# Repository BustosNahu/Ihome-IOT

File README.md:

# IHOME (spanish)

Este proyecto consta de una app con la cual deberias poder manejar toda tu casa,
hasta el momento serian cerraduras, camaras, y posibles cortinas .
El mismo posee desarrollo de hardware y modelado 3d de las cerraduras IOT.

## Tecnologias usadas

-   APLICACION MOVIL ANDROID 
En cuanto al desarrollo de la App mobile, la misma esta siendo desarrollada en idioma nativo Java, mediante la IDE de Android Studio. Estando solo disponible para dispotivios Android.

- APLICACION WEB

-   MICROCONTROLADOR
En cuanto al microcontrolador usado para la cerradura IOT de Ihome, fue utilizado un modulo ESP32s, el cual posee una antena para poder conectarse a la red wifi. 
El mismo fue programado en C++ con Arduino IDE. 

-   ESTUDIO Y DISEÑO UX/UI
La aplicacion de Ihome fue diseñada por un equipo certificado en UX/UI, creada y estudiada para un arquetipo de persona en especial, 
y que el publico de Ihome sienta una mayor comodidad y experiencia de usuario al utilizar la aplicacion. 

-   BASE DE DATOS
Ihome utiliza Firebase como base de datos para poder guardar toda su informacion. Desde fotos, datos de usuario, dispositivos vinculados entorno a la app mobile, y 
en torno a los micro controladores Firebase es utilizada para obtener los estados de los datos cargados por el usuario.

-   MODELADO 3D
El modelado 3d de Ihome fue llevado a cabo mediante la plataforma de modelado Fusion 360 de Auto Desk. 
Hasta el momento fue unicamente diseñado el modelo de la cerradura IOT. 

-   DISEÑO DE PCB ("Printed Circuit Board")
El diseño de PCB de Ihome fue llevado a cabo en la plataforma de Kicad, donde tuve que descargar los footprints de los componentes, modelos 3d, etc. 
Ya que la misma tiene un render que te permite ver los diseños en 3d. Ese mismo PCB terminado lo exportamos de Kicad y lo importamos en Fusion 360, 
para realizar un modelado 3d mas eficaz. 

## 🔗 Desarrolladores Links
- Desarrollador general del proyecto: 

Nahuel Alexander Bustos 

- Estudio y diseño del UX/UI:

Micaela Natasha Bustos

- Desarrollador de la aplicacion web del microcontrolador:

Joaquin Cervio

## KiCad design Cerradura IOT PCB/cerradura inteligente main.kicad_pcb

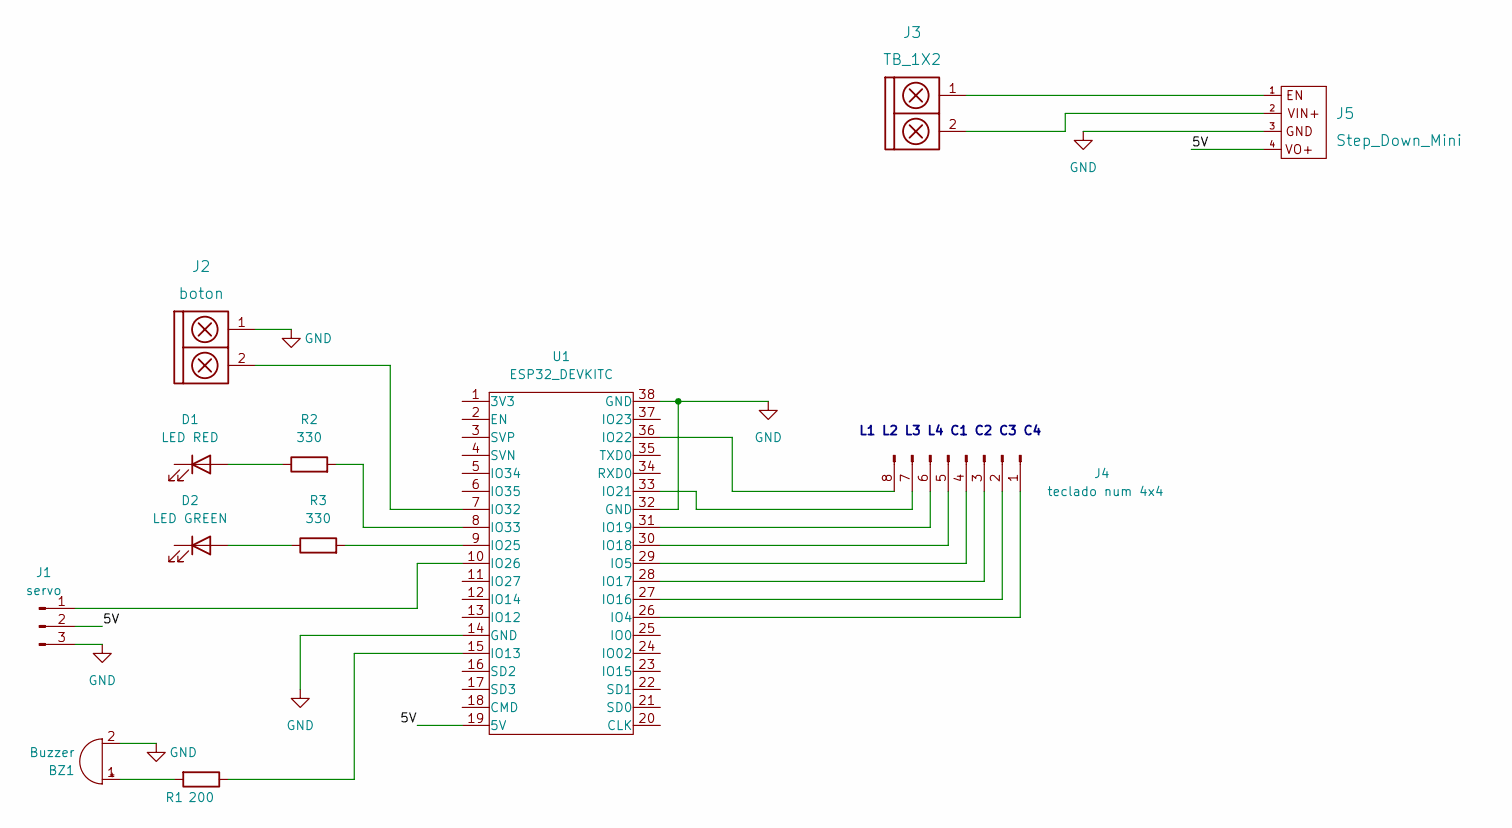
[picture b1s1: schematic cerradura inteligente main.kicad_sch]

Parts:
BZ1: Buzzer; Buzzer_Mallory_AST1109MLTRQ
D1: LED RED; led_3mm_red
D2: LED GREEN; led_3mm_green
J1: servo; Pin_Header_3
J2: boton; BORNERA2_AZUL
J3: TB_1X2; BORNERA2_AZUL
J4: teclado num 4x4; Pin_Header_Straight_1x08
J5: Step_Down_Mini
R1: 200; RES0.2
R2, R3: 330; RES0.2
U1: ESP32_DEVKITC

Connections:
/5V: J1.2, J5.4, U1.19 (5V)
GND: BZ1.2 (+), D1.1 (K), D2.1 (K), J1.3, J2.1, J5.3, U1.14 (GND), U1.32 (GND), U1.38 (GND)
unnamed: BZ1.1 (-), R1.2
unnamed: D1.2 (A), R2.1
unnamed: D2.2 (A), R3.1
unnamed: J1.1, U1.10 (IO26)
unnamed: J2.2, U1.7 (IO32)
unnamed: J3.1, J5.1
unnamed: J3.2, J5.2
unnamed: J4.1, U1.26 (IO4)
unnamed: J4.2, U1.27 (IO16)
unnamed: J4.3, U1.28 (IO17)
unnamed: J4.4, U1.29 (IO5)
unnamed: J4.5, U1.30 (IO18)
unnamed: J4.6, U1.31 (IO19)
unnamed: J4.7, U1.33 (IO21)
unnamed: J4.8, U1.36 (IO22)
unnamed: R2.2, U1.8 (IO33)
unnamed: R3.2, U1.9 (IO25)
unnamed: R1.1, U1.15 (IO13)

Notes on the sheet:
L1 L2 L3 L4 C1 C2 C3 C4

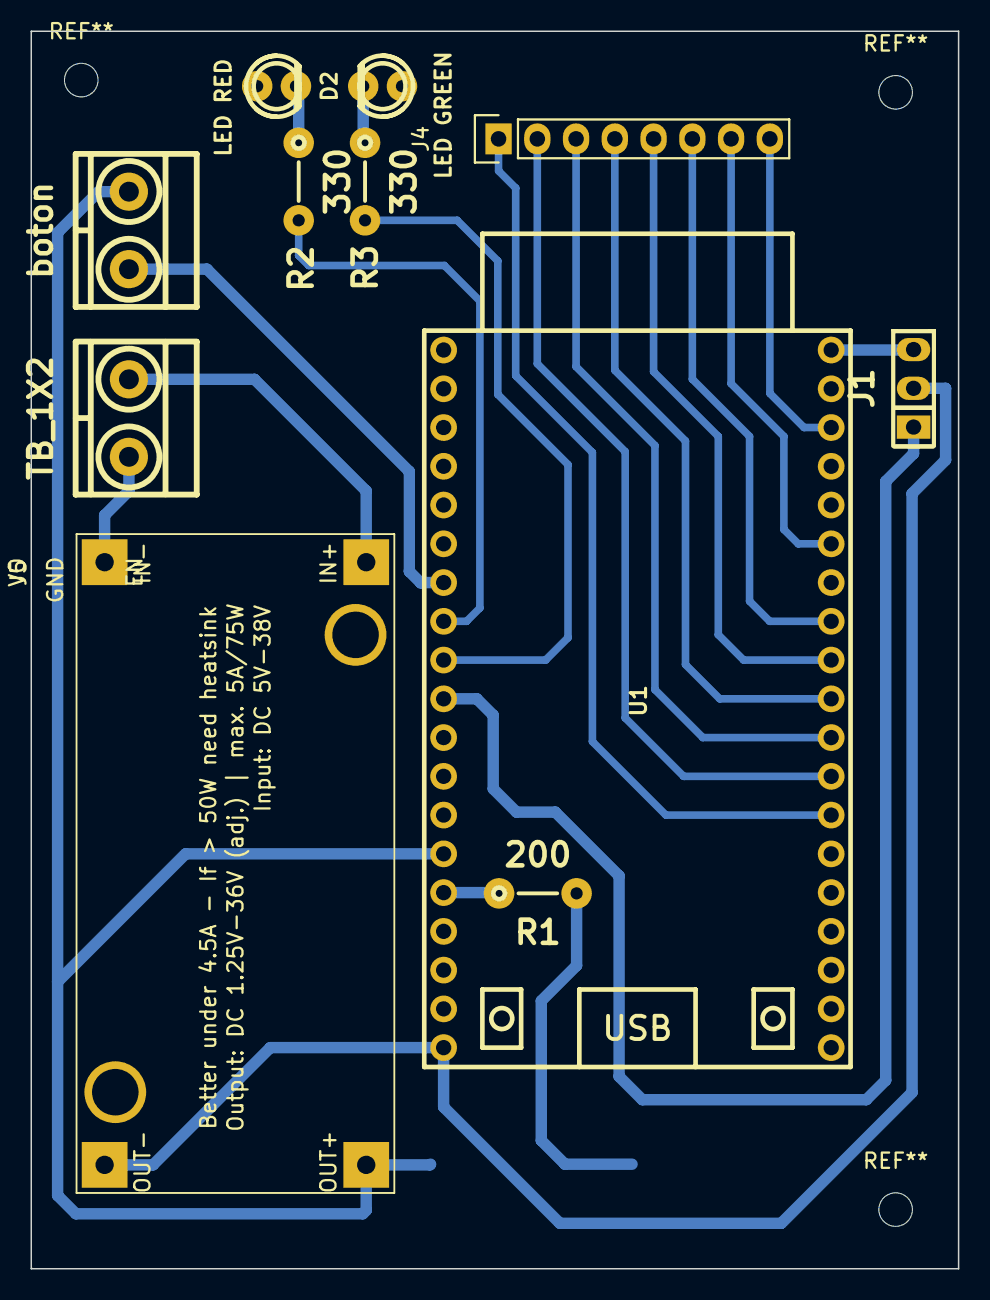
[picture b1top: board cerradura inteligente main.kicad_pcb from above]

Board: 2 copper layers, 60.8 x 81.1 mm, 12 parts (1 on the bottom side), 20 nets.

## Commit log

2023-01-17 Login y Register conectados con database
2023-01-18 Regiser casi terminado-Parte del home conectado al database
2023-01-19 Subo recycler view a terminar y conectar a base de datos
2023-02-20 actualizo
2023-03-06 agrego
2023-03-15 Foto de perfil conectada a storage y funcionando falta terminar save changes de editUser
2023-03-16 EditProfileActivity terminada funcionando al 100% faltan terminar recycler views / conectarlos al database Cambiar iconos y animacion del bottomNavView
2023-03-16 EditProfileActivity terminada funcionando al 100% faltan terminar recycler views / conectarlos al database cambiar animacion del bottomNavView
2023-04-06 ilustracion de fav screen terminado
2023-04-10 Subo archivos
2023-04-10 Actualizo PCB
2023-05-04 terminar recycler y dialog
2023-05-05 EL RECYCLER
2023-05-06 Funciona recycler view, con metodo onItemClickListener. Tambien el add newRoom con su nombre por el momento, firebase creando listas de objetos todo OK
2023-05-09 arreglar RegisterActivity y login
2023-05-10 funciona register y login, terminar rooms fragments y resto de UI
2023-05-10 temrinar switch case RoomAdapter
2023-05-15 switchcase terminado
2023-05-15 terminar bottom navigation
2023-05-16 termine alert dialog
2023-05-18 Subo proyecto
2023-05-23 terminar request del clima api retrofit
2023-05-24 Anda
2023-06-05 have done: -Add new activity in kotlin with jetpack compose (RoomsActivity)
    still needed:
    -Make UI and add new fragment screen to add new devices, and finish lazyRow
2023-06-06 have done: -rooms screen connected to the databse and works fine
    still needed:
    -Make UI and add new fragment screen to add new devices, and finish lazyRow
    -Add device screen, connect with database, and finish ui room screen
2023-06-10 have done: -screen room almost finishe
    still needed:
    -Make controller devices screen
2023-06-12 have done: -locker state change is working well
    still needed:
    -delete rooms, devices, finish UI
2023-09-20 Login finished
